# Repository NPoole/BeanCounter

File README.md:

# BeanCounter

[![CC BY-SA 4.0][cc-by-sa-shield]][cc-by-sa]

BeanCounter is an SMT parts counter that fits in your pocket. It’s battery powered and uses two IR photointerrupters to count parts about as fast as you can pull them through. It works with any opaque, 8-mm-wide carrier tape up to 2 mm in height, which covers most 0805-or-smaller LEDs and passives, as well as SOT23 transistors. It’s an affordable SMT tape counter without unnecessary bells and whistles.

<p align="center"><em>Photo Courtesy of Hannah Wood/SparkFun Electronics</em></p>

## Available Now at [Crowd Supply](https://www.crowdsupply.com/great-big-factory/beancounter), [Mouser](https://www.mouser.com/c/electromechanical/industrial-automation/?m=Great%20Big%20Factory), and [SparkFun](https://www.sparkfun.com/products/21738)

To use BeanCounter, simply turn it on and start pulling tape through. It will immediately begin counting your parts using one of two modes:

* Inventory Mode - Using just one sensor, BeanCounter polls at its fastest rate, allowing you to count long tapes and partial reels very quickly.
* Dispense Mode - With both sensors active, BeanCounter can detect the direction in which you are pulling tape, which allows it to count upward in one direction and downward in the other. This feature is useful in kitting contexts where you may be cutting fixed quantities off the end of a full reel.
Part pitch is configurable in either mode, so you can accurately count any part that physically fits through the counter.

Digging a little deeper, what BeanCounter actually does is count feed holes and divide by the part pitch. Because it cannot differentiate between parts and empty pockets, you will need to ensure that it begins counting after empty tape has been pulled through and stops counting before it reaches the tail. To help with this, we’ve added a "pause" button that you can use to freeze the count while pulling empty tape.

[cc-by-sa]: http://creativecommons.org/licenses/by-sa/4.0/
[cc-by-sa-shield]: https://img.shields.io/badge/License-CC%20BY--SA%204.0-lightgrey.svg

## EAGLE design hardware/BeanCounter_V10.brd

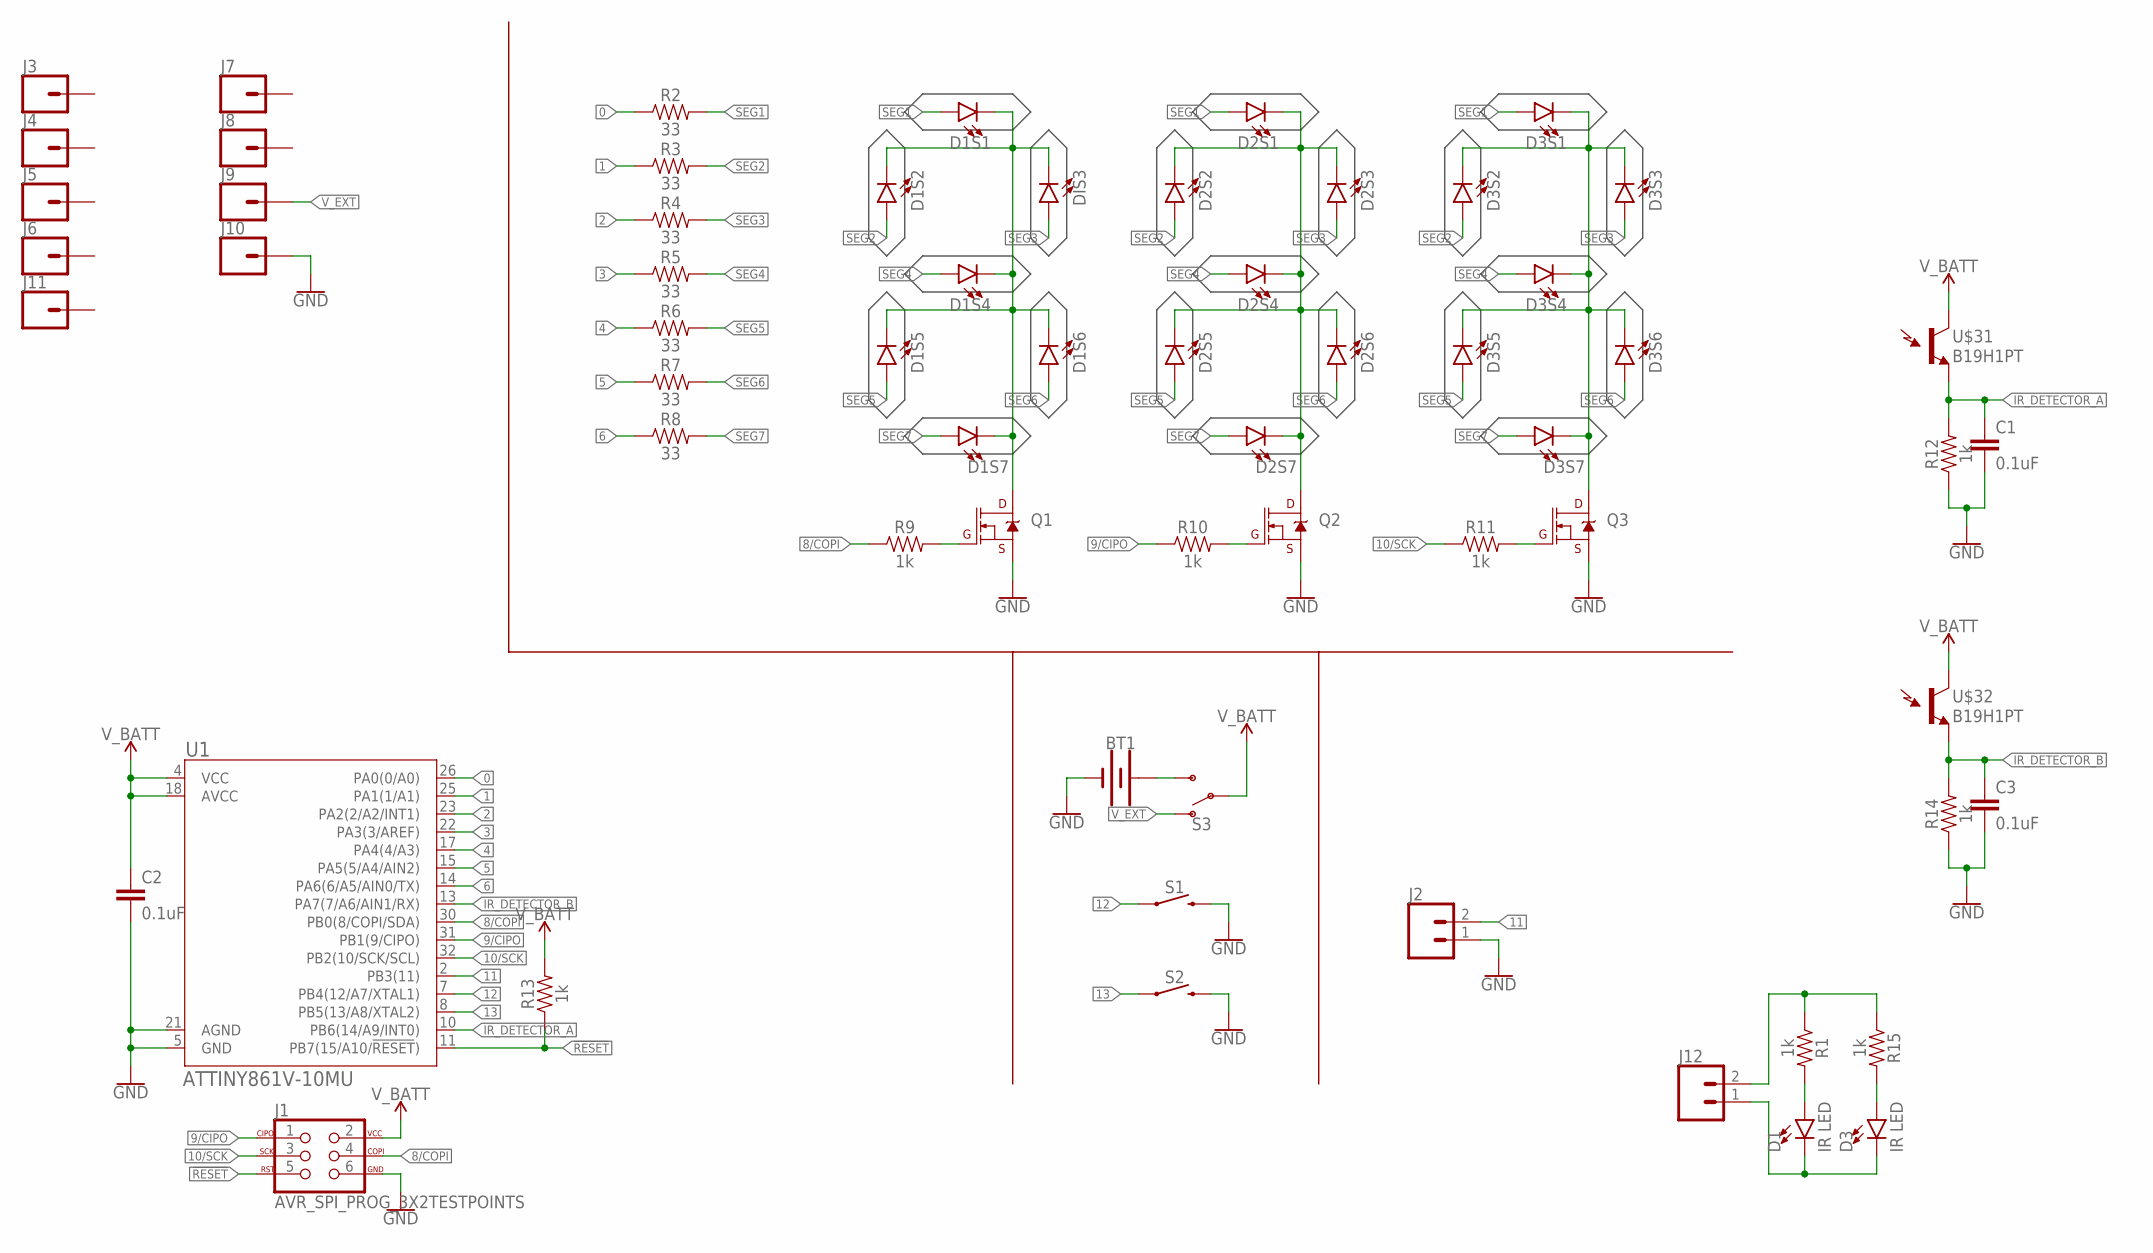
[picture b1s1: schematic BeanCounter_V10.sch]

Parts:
BT1: BATTERY-20MM_SMD_4LEGS_OVERPASTE_INNER; BATTCON_20MM_4LEGS_OVERPASTE_INNER
C1, C2, C3: 0.1uF; 0603
D1, D3: IR LED; LED-0603
D1S1, D1S2, D1S4, D1S5, D1S6, D1S7, D2S1, D2S2, D2S3, D2S4, D2S5, D2S6, D2S7, D3S1, D3S2, D3S3, D3S4, D3S5, D3S6, D3S7: LED0603; LED-0603
DIS3: LED0603; LED-0603
J1: AVR_SPI_PROG_3X2TESTPOINTS; 2X3_TEST_POINTS
J2, J12: CONN_02; 1X02
J3, J4, J5, J6, J7, J8, J9, J10, J11: CONN_01; 1X01
Q1, Q2, Q3: 220mA/50V/3.5Ω; SOT23-3
R1, R9, R10, R11, R12, R13, R14, R15: 1k; 0603
R2, R3, R4, R5, R6, R7, R8: 33; 0603
S1, S2: MOMENTARY-SWITCH-SPST-SMD-5.2MM-TALL; TACTILE_SWITCH_SMD_5.2MM
S3: SWITCH-SPDT-SMD-RIGHT-ANGLE; SWITCH_SPST_SMD_A
U1: ATTINY861V-10MU; 32M1-A_ATM
U$31, U$32: B19H1PT; HARVATEK_DETECTOR

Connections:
0: R2.1, U1.26 (PA0(0/A0))
1: R3.1, U1.25 (PA1(1/A1))
2: R4.1, U1.23 (PA2(2/A2/INT1))
3: R5.1, U1.22 (PA3(3/AREF))
4: R6.1, U1.17 (PA4(4/A3))
5: R7.1, U1.15 (PA5(5/A4/AIN2))
6: R8.1, U1.14 (PA6(6/A5/AIN0/TX))
8/COPI: J1.4, R9.1, U1.30 (PB0(8/COPI/SDA))
9/CIPO: J1.1, R10.1, U1.31 (PB1(9/CIPO))
10/SCK: J1.3, R11.1, U1.32 (PB2(10/SCK/SCL))
11: J2.2, U1.2 (PB3(11))
12: S1.1, U1.7 (PB4(12/A7/XTAL1))
13: S2.1, U1.8 (PB5(13/A8/XTAL2))
!RESET: J1.5, R13.1, U1.11 (PB7(15/A10/!RESET!))
GND: BT1.2 (-), C1.2, C2.2, C3.2, J1.6, J2.1, J10.1, Q1.2 (S), Q2.2 (S), Q3.2 (S), R12.1, R14.1, S1.3 (2), S2.3 (2), U1.5 (GND), U1.21 (AGND)
IR_DETECTOR_A: C1.1, R12.2, U1.10 (PB6(14/A9/INT0)), U$31.P$2 (E1)
IR_DETECTOR_B: C3.1, R14.2, U1.13 (PA7(7/A6/AIN1/RX)), U$32.P$2 (E1)
unnamed: BT1.1 (+), S3.3 (S)
unnamed: D1S1.C, D1S2.C, D1S4.C, D1S5.C, D1S6.C, D1S7.C, DIS3.C, Q1.3 (D)
unnamed: Q2.1 (G), R10.2
unnamed: Q1.1 (G), R9.2
unnamed: D2S1.C, D2S2.C, D2S3.C, D2S4.C, D2S5.C, D2S6.C, D2S7.C, Q2.3 (D)
unnamed: Q3.1 (G), R11.2
unnamed: D3S1.C, D3S2.C, D3S3.C, D3S4.C, D3S5.C, D3S6.C, D3S7.C, Q3.3 (D)
unnamed: D3.A, R15.2
unnamed: D1.A, R1.2
unnamed: J12.2, R1.1, R15.1
unnamed: D1.C, D3.C, J12.1
SEG1: D1S1.A, D2S1.A, D3S1.A, R2.2
SEG2: D1S2.A, D2S2.A, D3S2.A, R3.2
SEG3: D2S3.A, D3S3.A, DIS3.A, R4.2
SEG4: D1S4.A, D2S4.A, D3S4.A, R5.2
SEG5: D1S5.A, D2S5.A, D3S5.A, R6.2
SEG6: D1S6.A, D2S6.A, D3S6.A, R7.2
SEG7: D1S7.A, D2S7.A, D3S7.A, R8.2
V_BATT: C2.1, J1.2, R13.2, S3.2, U1.4 (VCC), U1.18 (AVCC), U$31.P$1 (C1), U$32.P$1 (C1)
V_EXT: J9.1, S3.1 (O)

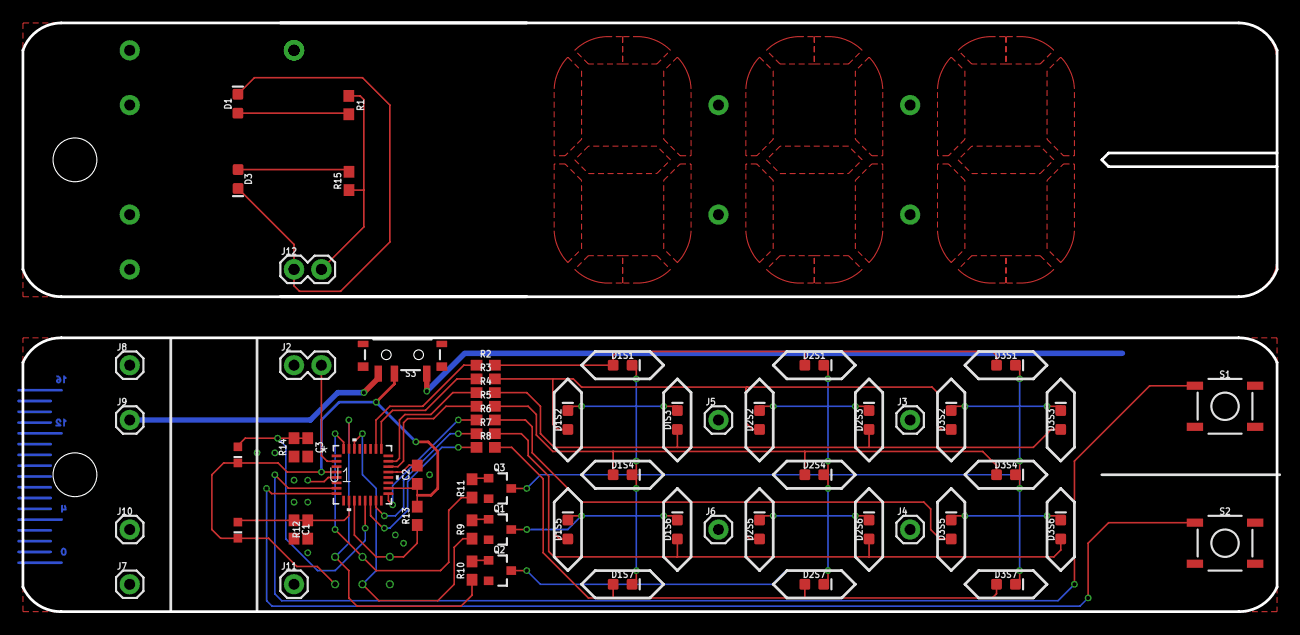
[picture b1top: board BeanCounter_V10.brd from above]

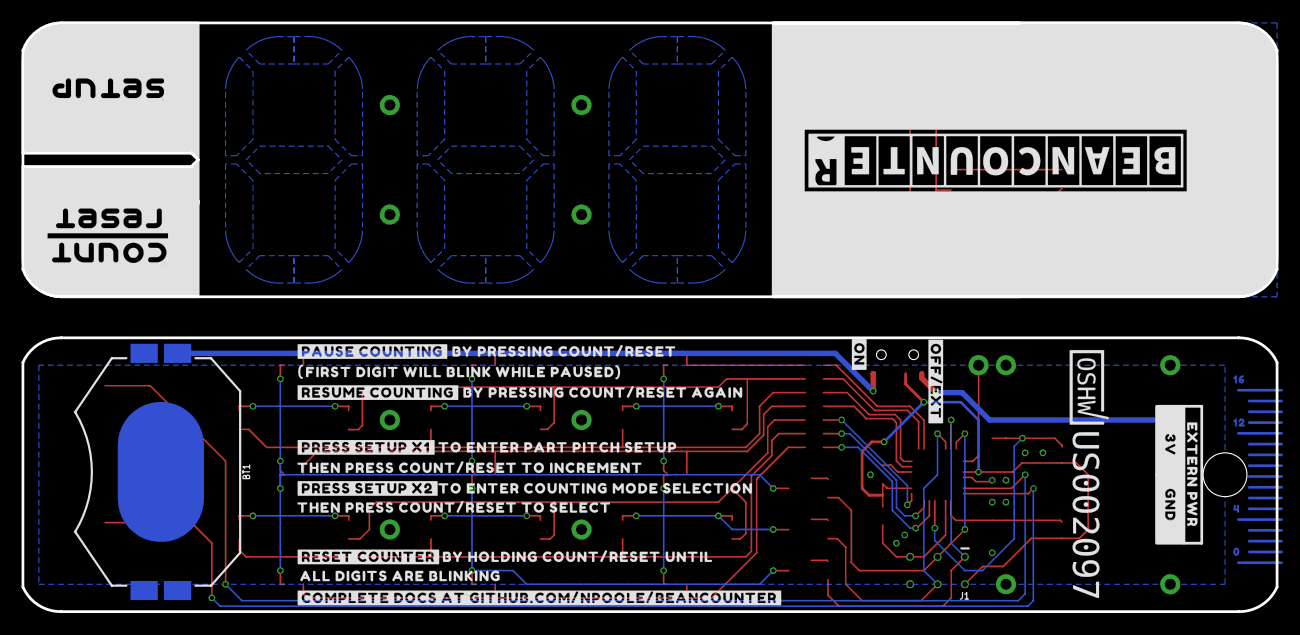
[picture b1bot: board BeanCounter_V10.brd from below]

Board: 2 copper layers, 116.3 x 54.6 mm, 93 parts (32 on the bottom side), 37 nets.

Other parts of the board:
U$1: OSHWBC#SVG0
U$2: EXTERN_PWR0
U$3: #PAUSE_COUNTING#0
U$4: #PRESS_SETUP_X1#0
U$5: 00
U$6: #_3V#0
U$7: #_GND#0
U$8: THEN_PRESS_COUNT#RESET_TO_INCREMENT0
U$9: BY_PRESSING_COUNT#RESET0
U$10: FIRST_DIGIT_WILL_BLINK_WHILE_PAUSED#_0
U$11: #_0
U$12: #RESUME_COUNTING#0
U$13: BY_PRESSING_COUNT#RESET_AGAIN0
U$14: TO_ENTER_PART_PITCH_SETUP0
U$15: #PRESS_SETUP_X2#0
U$16: TO_ENTER_COUNTING_MODE_SELECTION0
U$17: THEN_PRESS_COUNT#RESET_TO_SELECT0
U$18: #RESET_COUNTER#0
U$19: BY_HOLDING_COUNT#RESET_UNTIL0
U$20: 40
U$21: 120
U$22: 160
U$23: #ON#0
U$24: #OFF#EXT#0
U$25: ALL_DIGITS_ARE_BLINKING0
U$26: #COMPLETE_DOCS_AT_GITHUB#COM#NPOOLE#BEANCOUNTER#0
U$27: #COUNT#0
U$28: #RESET#0
U$29: #SETUP#0
U$30: LOGO#SVG0

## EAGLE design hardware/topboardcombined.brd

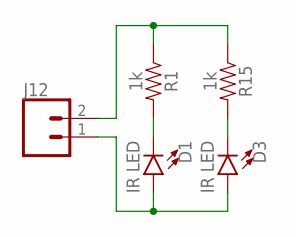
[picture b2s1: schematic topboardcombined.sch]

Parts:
D1, D3: IR LED; LED-0603
J12: CONN_02; 1X02
R1, R15: 1k; 0603

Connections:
unnamed: J12.2, R1.1, R15.1
unnamed: D1.C, R1.2
unnamed: D3.C, R15.2
unnamed: D1.A, D3.A, J12.1

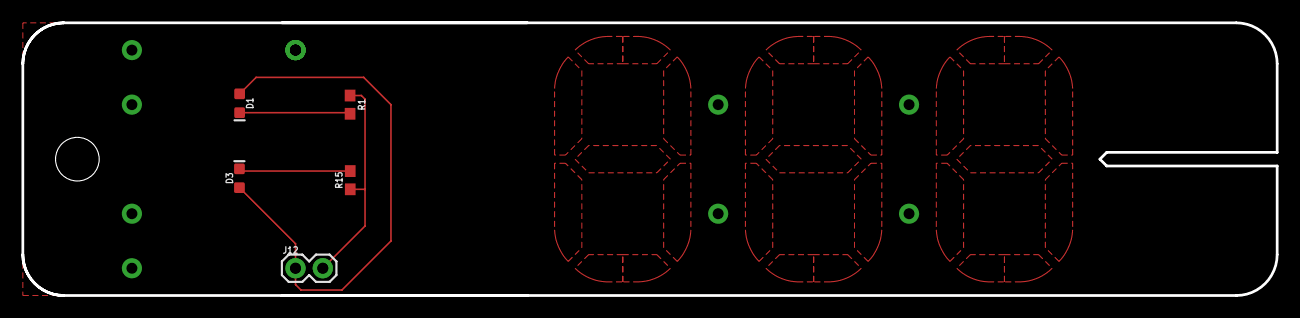
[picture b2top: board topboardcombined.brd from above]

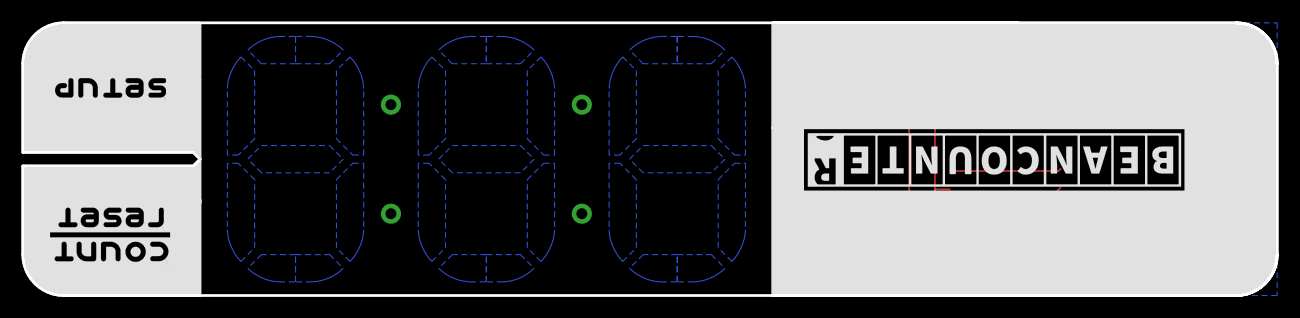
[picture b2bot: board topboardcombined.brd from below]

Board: 2 copper layers, 116.8 x 25.4 mm, 9 parts (4 on the bottom side), 4 nets.

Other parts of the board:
U$1: #COUNT#0
U$2: #RESET#0
U$3: #SETUP#0
U$4: LOGO#SVG0

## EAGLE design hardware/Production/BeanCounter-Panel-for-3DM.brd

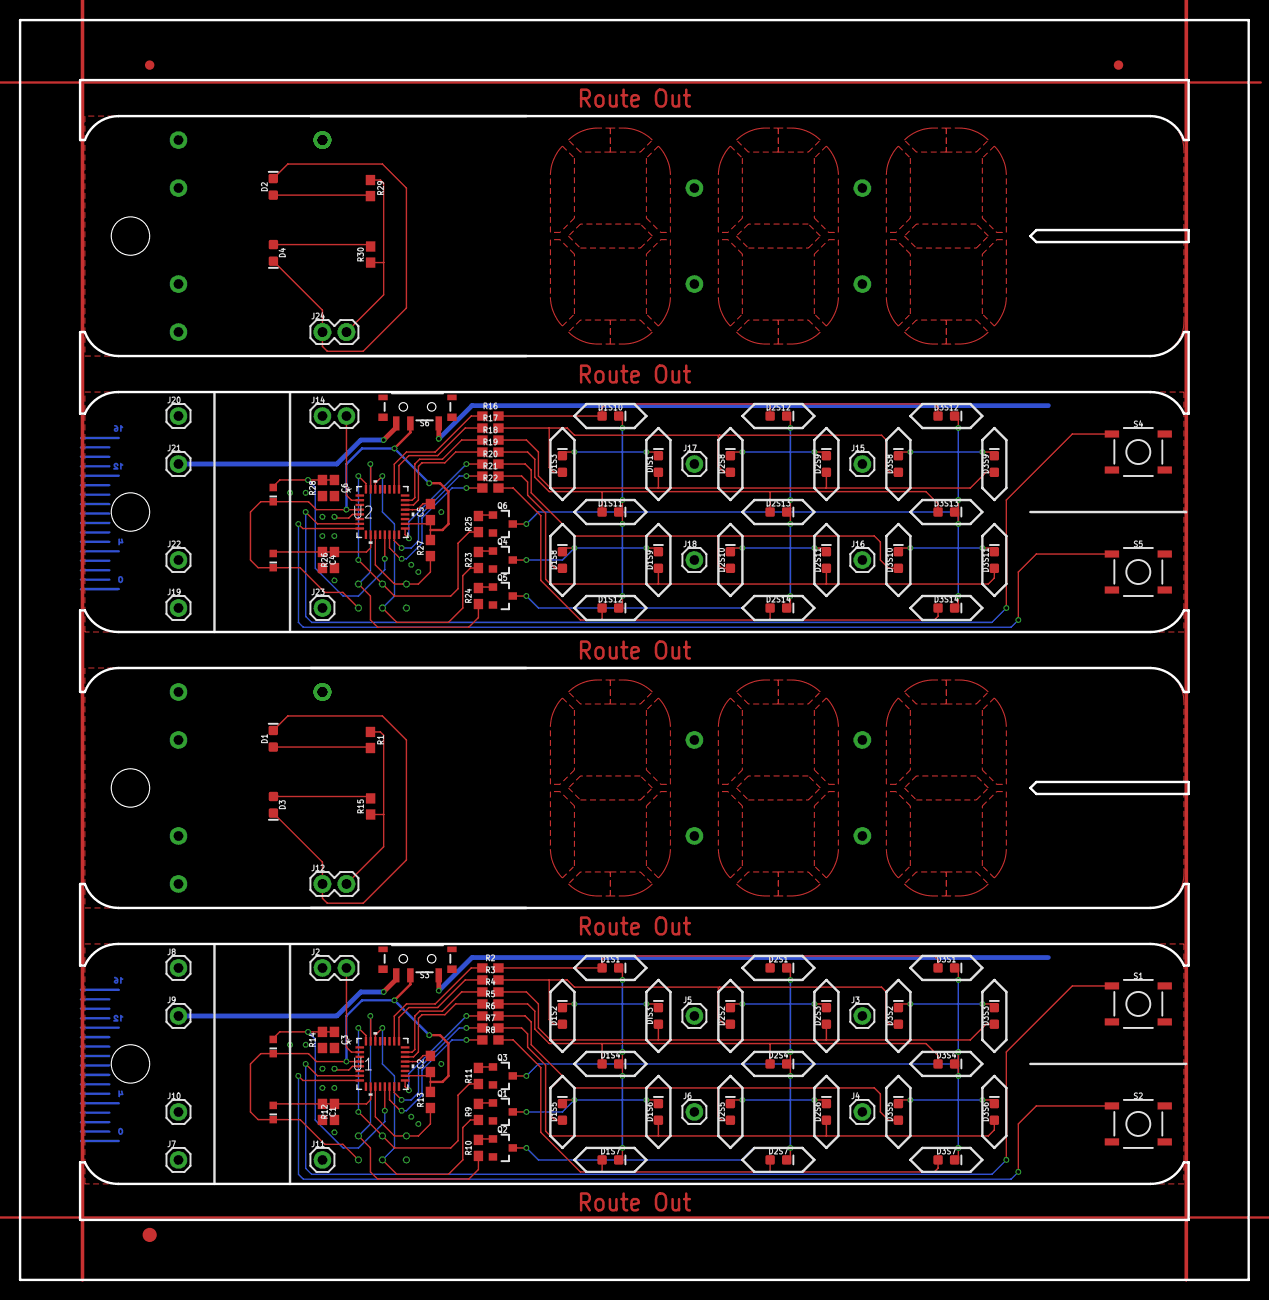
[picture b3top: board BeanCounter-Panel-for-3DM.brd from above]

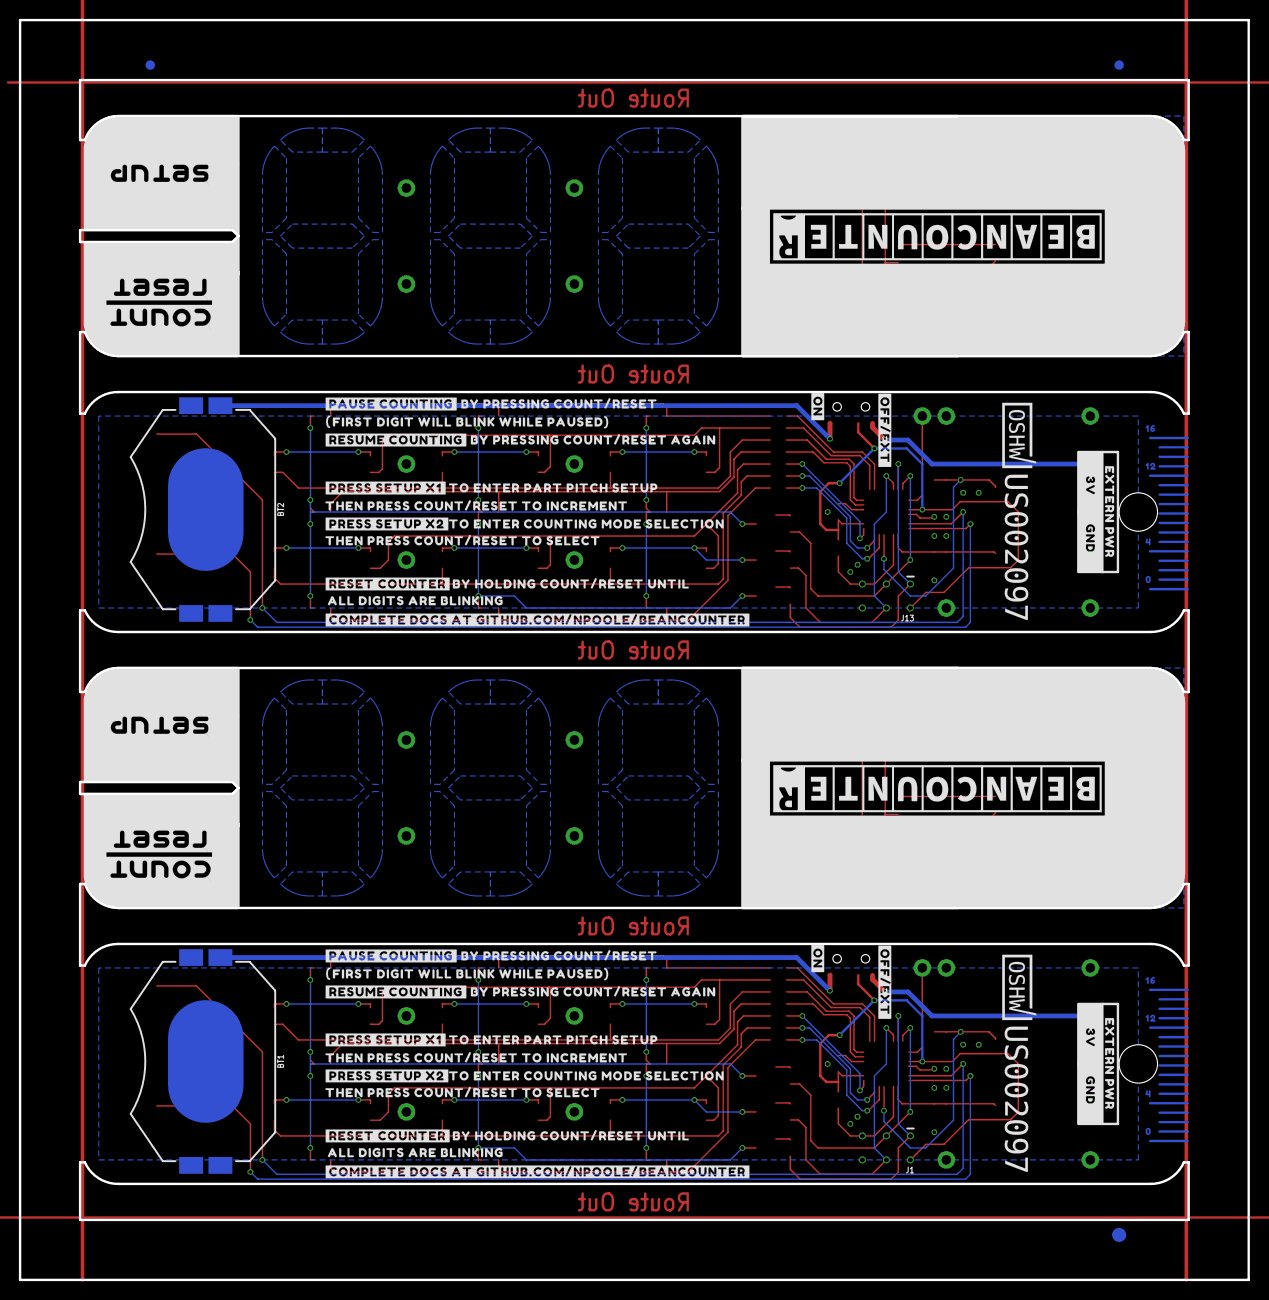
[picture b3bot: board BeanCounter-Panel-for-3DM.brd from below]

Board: 2 copper layers, 130.0 x 133.3 mm, 192 parts (67 on the bottom side), 74 nets.

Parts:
BT1, BT2: BATTCON_20MM_4LEGS_OVERPASTE_INNER
C1, C2, C3, C4, C5, C6: 0.1uF; 0603
D1, D2, D3, D4: IR LED; LED-0603
D1S1, D1S2, D1S3, D1S4, D1S5, D1S6, D1S7, D1S8, D1S9, D1S10, D1S11, D1S12, D2S1, D2S2, D2S3, D2S4, D2S5, D2S6, D2S7, D2S8, D2S9, D2S10, D2S11, D2S12, D2S13, D2S14, D3S1, D3S2, D3S3, D3S4, D3S5, D3S6, D3S7, D3S8, D3S9, D3S10, D3S11, D3S12, D3S13, D3S14: LED-0603
DIS1, DIS3: LED-0603
E$1, E$2, E$3, E$4: FIDUCIAL-1X2
E$5, E$6: FIDUCIAL-1.5X3
J1, J13: AVR_SPI_PROG_3X2TESTPOINTS; 2X3_TEST_POINTS
J2, J12, J14, J24: 1X02
J3, J4, J5, J6, J7, J8, J9, J10, J11, J15, J16, J17, J18, J19, J20, J21, J22, J23: 1X01
Q1, Q2, Q3, Q4, Q5, Q6: 220mA/50V/3.5Ω; SOT23-3
R1, R9, R10, R11, R12, R13, R14, R15, R23, R24, R25, R26, R27, R28, R29, R30: 1k; 0603
R2, R3, R4, R5, R6, R7, R8, R16, R17, R18, R19, R20, R21, R22: 33; 0603
S1, S2, S4, S5: MOMENTARY-SWITCH-SPST-SMD-5.2MM-TALL; TACTILE_SWITCH_SMD_5.2MM
S3, S6: SWITCH_SPST_SMD_A
U1, U2: ATTINY861V-10MU; 32M1-A_ATM
U$1, U$41: OSHWBC#SVG0
U$2, U$42: EXTERN_PWR0
U$3, U$43: #PAUSE_COUNTING#0
U$4, U$49: #PRESS_SETUP_X1#0
U$5, U$35: 00
U$6, U$33: #_3V#0
U$7, U$34: #_GND#0
U$8, U$51: THEN_PRESS_COUNT#RESET_TO_INCREMENT0
U$9, U$44: BY_PRESSING_COUNT#RESET0
U$10, U$45: FIRST_DIGIT_WILL_BLINK_WHILE_PAUSED#_0
U$11, U$46: #_0
U$12, U$47: #RESUME_COUNTING#0
U$13, U$48: BY_PRESSING_COUNT#RESET_AGAIN0
U$14, U$50: TO_ENTER_PART_PITCH_SETUP0
U$15, U$52: #PRESS_SETUP_X2#0
U$16, U$53: TO_ENTER_COUNTING_MODE_SELECTION0
U$17, U$54: THEN_PRESS_COUNT#RESET_TO_SELECT0
U$18, U$55: #RESET_COUNTER#0
U$19, U$56: BY_HOLDING_COUNT#RESET_UNTIL0
U$20, U$36: 40
U$21, U$37: 120
U$22, U$38: 160
U$23, U$39: #ON#0
U$24, U$40: #OFF#EXT#0
U$25, U$57: ALL_DIGITS_ARE_BLINKING0
U$26, U$58: #COMPLETE_DOCS_AT_GITHUB#COM#NPOOLE#BEANCOUNTER#0
U$27, U$59: #COUNT#0
U$28, U$60: #RESET#0
U$29, U$61: #SETUP#0
U$30, U$62: LOGO#SVG0
U$31, U$32, U$63, U$64: B19H1PT; HARVATEK_DETECTOR

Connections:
0: R2.1, U1.26
1: R3.1, U1.25
2: R4.1, U1.23
3: R5.1, U1.22
4: R6.1, U1.17
5: R7.1, U1.15
6: R8.1, U1.14
7: R16.1, U2.26
8: R17.1, U2.25
8/COPI: J1.4, R9.1, U1.30
8/COPI1: J13.4, R23.1, U2.30
9: R18.1, U2.23
9/CIPO: J1.1, R10.1, U1.31
9/CIPO1: J13.1, R24.1, U2.31
10: R19.1, U2.22
10/SCK: J1.3, R11.1, U1.32
10/SCK1: J13.3, R25.1, U2.32
11: J2.2, U1.2
12: S1.1, U1.7
13: S2.1, U1.8
14: R20.1, U2.17
15: R21.1, U2.15
16: R22.1, U2.14
17: J14.2, U2.2
18: S4.1, U2.7
19: S5.1, U2.8
!RESET: J1.5, R13.1, U1.11
!RESET1: J13.5, R27.1, U2.11
GND: BT1.2, C1.2, C2.2, C3.2, J1.6, J2.1, J10.1, Q1.2, Q2.2, Q3.2, R12.1, R14.1, S1.3, S2.3, U1.5, U1.21
GND1: BT2.2, C4.2, C5.2, C6.2, J13.6, J14.1, J22.1, Q4.2, Q5.2, Q6.2, R26.1, R28.1, S4.3, S5.3, U2.5, U2.21
IR_DETECTOR_A: C1.1, R12.2, U1.10, U$31.P$2
IR_DETECTOR_A1: C4.1, R26.2, U2.10, U$63.P$2
IR_DETECTOR_B: C3.1, R14.2, U1.13, U$32.P$2
IR_DETECTOR_B1: C6.1, R28.2, U2.13, U$64.P$2
unnamed: BT1.1, S3.3
unnamed: D1S1.C, D1S2.C, D1S4.C, D1S5.C, D1S6.C, D1S7.C, DIS3.C, Q1.3
unnamed: Q2.1, R10.2
unnamed: Q1.1, R9.2
unnamed: D2S1.C, D2S2.C, D2S3.C, D2S4.C, D2S5.C, D2S6.C, D2S7.C, Q2.3
unnamed: Q3.1, R11.2
unnamed: D3S1.C, D3S2.C, D3S3.C, D3S4.C, D3S5.C, D3S6.C, D3S7.C, Q3.3
unnamed: Q4.1, R23.2
unnamed: D1S3.C, D1S8.C, D1S9.C, D1S10.C, D1S11.C, D1S12.C, DIS1.C, Q4.3
unnamed: D2S8.C, D2S9.C, D2S10.C, D2S11.C, D2S12.C, D2S13.C, D2S14.C, Q5.3
unnamed: D3S8.C, D3S9.C, D3S10.C, D3S11.C, D3S12.C, D3S13.C, D3S14.C, Q6.3
unnamed: D3.A, R15.2
unnamed: D1.A, R1.2
unnamed: Q5.1, R24.2
unnamed: Q6.1, R25.2
unnamed: BT2.1, S6.3
unnamed: J12.2, R1.1, R15.1
unnamed: D1.C, D3.C, J12.1
unnamed: J24.2, R29.1, R30.1
unnamed: D2.C, D4.C, J24.1
unnamed: D4.A, R30.2
unnamed: D2.A, R29.2
SEG1: D1S1.A, D2S1.A, D3S1.A, R2.2
SEG2: D1S2.A, D2S2.A, D3S2.A, R3.2
SEG3: D2S3.A, D3S3.A, DIS3.A, R4.2
SEG4: D1S4.A, D2S4.A, D3S4.A, R5.2
SEG5: D1S5.A, D2S5.A, D3S5.A, R6.2
SEG6: D1S6.A, D2S6.A, D3S6.A, R7.2
SEG7: D1S7.A, D2S7.A, D3S7.A, R8.2
SEG8: D1S10.A, D2S12.A, D3S12.A, R16.2
SEG9: D1S11.A, D2S13.A, D3S13.A, R19.2
SEG10: D1S3.A, D2S8.A, D3S8.A, R17.2
SEG11: D2S9.A, D3S9.A, DIS1.A, R18.2
SEG12: D1S9.A, D2S11.A, D3S11.A, R21.2
SEG13: D1S8.A, D2S10.A, D3S10.A, R20.2
SEG14: D1S12.A, D2S14.A, D3S14.A, R22.2
V_BATT: C2.1, J1.2, R13.2, S3.2, U1.4, U1.18, U$31.P$1, U$32.P$1
V_BATT1: C5.1, J13.2, R27.2, S6.2, U2.4, U2.18, U$63.P$1, U$64.P$1
V_EXT: J9.1, S3.1
V_EXT1: J21.1, S6.1

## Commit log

2021-11-06 Initial Commit v0.01
2021-11-10 cleaning up before giving out the link
2021-11-26 Pushing PDFs for non EAGLE users to peek at the docs
    Also, firmware from the Twitter demo
2021-11-30 Board and Code changes. Close to v1.0
    Board and Code changes. Close to v1.0
2022-01-18 V10 Firmware
2022-01-22 Starting to develop doc/site
2022-01-22 Doing radical things to unbork on Win machine
    Pardon the mess
2022-01-22 Maybe this fixes things
2022-01-23 [docs] Testing a scroll feature on mobile
2022-01-28 Incremental Webpage Improvements
2022-01-29 Incremental Website Changes
    It's a mess
2022-01-29 Incremental Webpage Improvements
    Still not finished, less of a mess
2022-04-04 Housekeeping
    - Remove prototypes
    - Remove EAGLE backup files
    - Archive GHPages site
    - Commit 3D CAD
2022-04-29 Create LICENSE
2022-08-05 Cleanup, add support files
2023-07-15 Fix orientation of '1'
    Changed the '1' from left justification to right justification
2023-07-28 Uploading missing docs
2023-11-09 Add programming batch file
2023-11-11 Add disassembly instructions
2026-01-10 Upload compliance docs
    I thought these were in the repo but I couldn't find them

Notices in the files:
parts and their libraries:
SparkFun-Switches: Licensing: Creative Commons ShareAlike 4.0 International - https://creativecommons.org/licenses/by-sa/4.0
COPYRIGHT: Copyright (C) 2021 Ultra Librarian. All rights reserved.
